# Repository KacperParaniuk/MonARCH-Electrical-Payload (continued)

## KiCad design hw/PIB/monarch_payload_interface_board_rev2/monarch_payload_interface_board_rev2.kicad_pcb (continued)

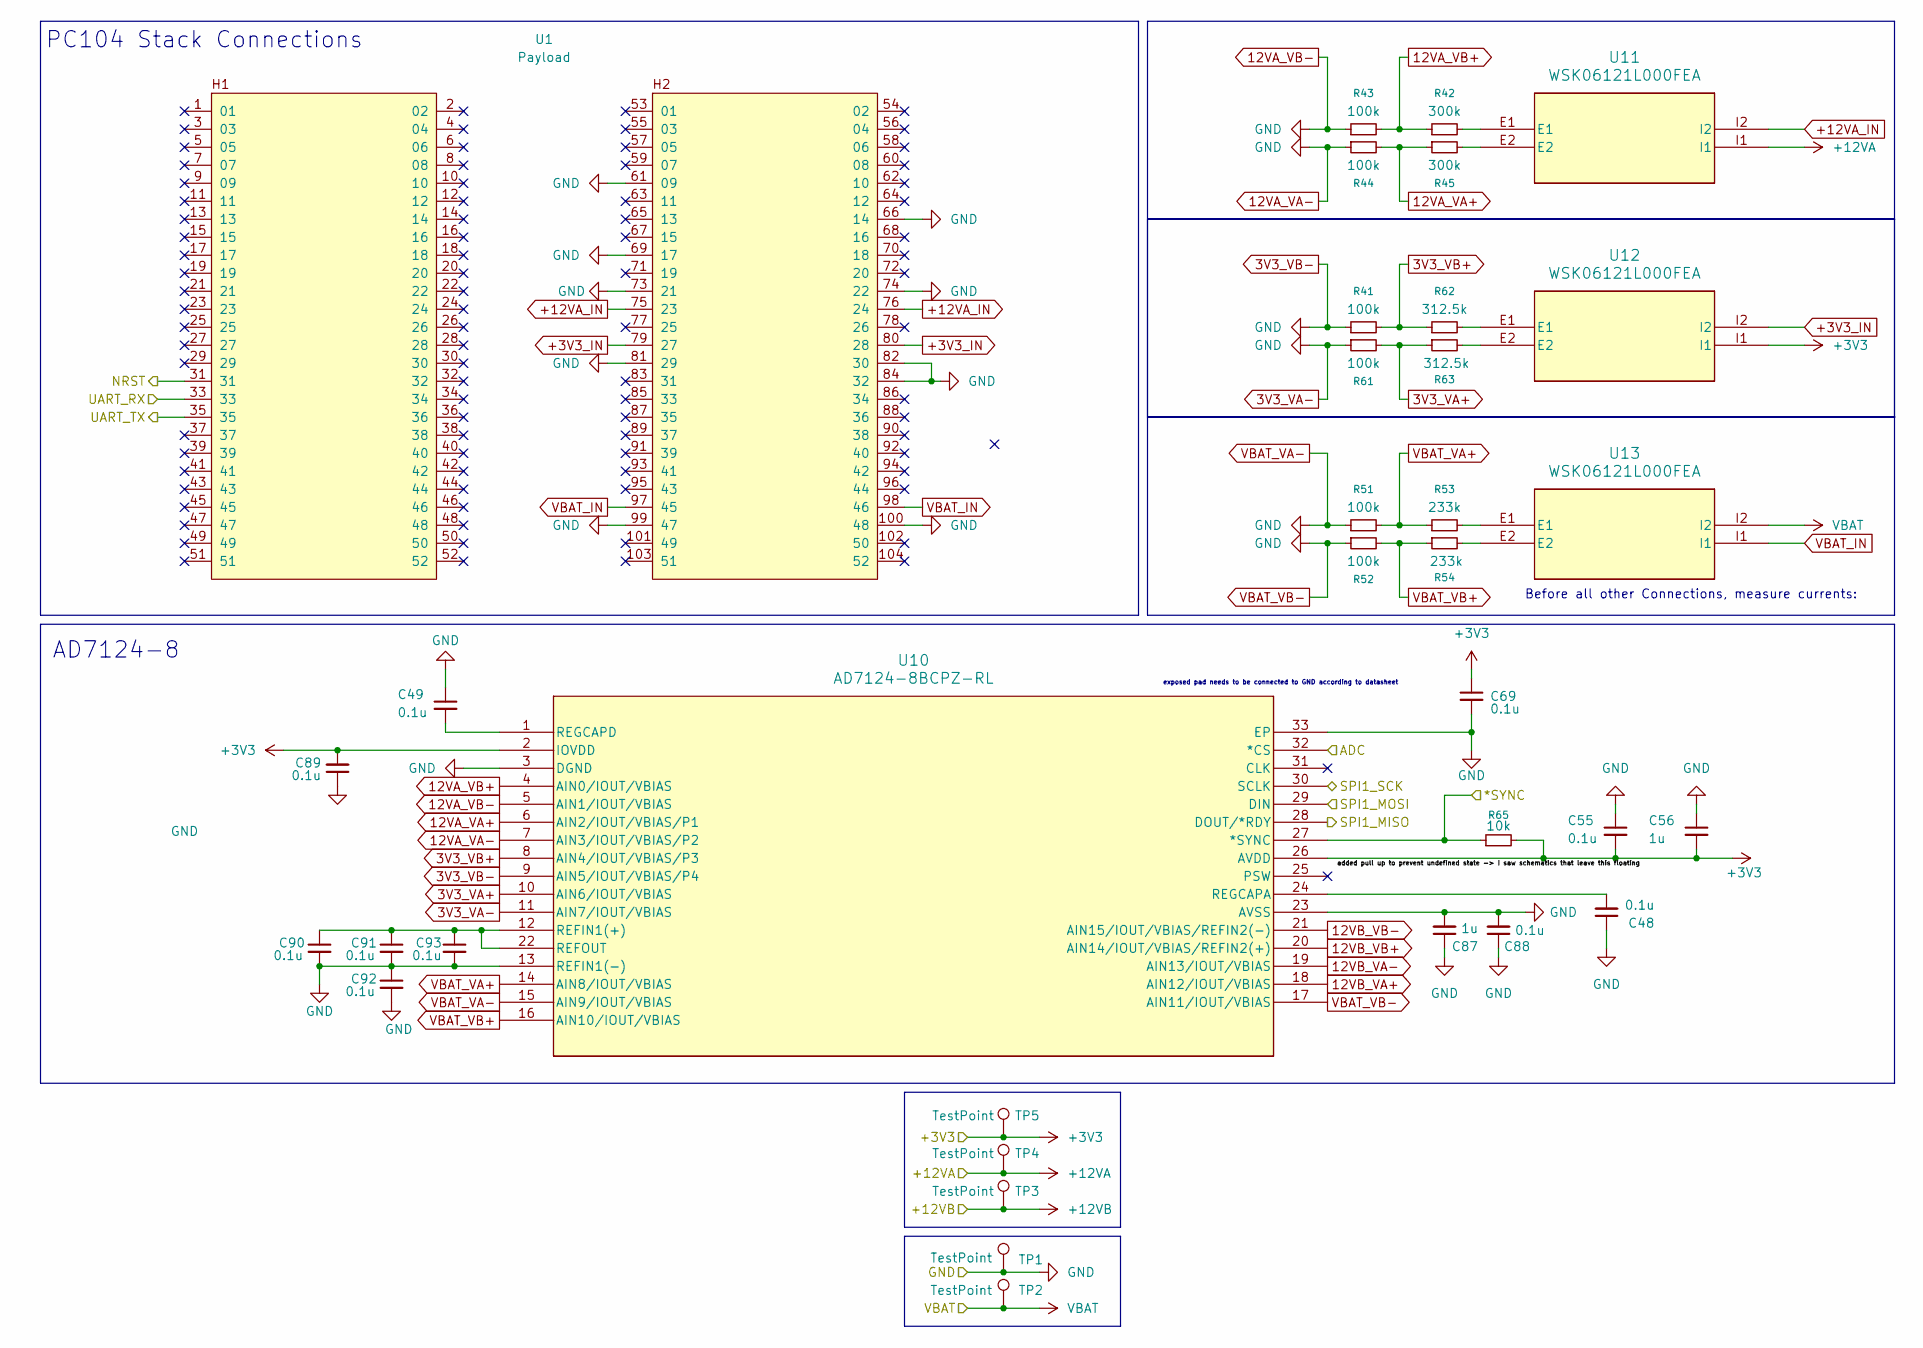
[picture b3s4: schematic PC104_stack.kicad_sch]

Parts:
C48, C49, C55, C69, C88, C89, C90, C91, C92, C93: 0.1u; C_0603_1608Metric
C56, C87: 1u; C_0603_1608Metric
R41, R43, R44, R51, R52, R61: 100k; R_0603_1608Metric
R42, R45: 300k; R_0603_1608Metric
R53, R54: 233k; R_0603_1608Metric
R62, R63: 312.5k; R_0603_1608Metric
R65: 10k; R_0603_1608Metric
TP1, TP2, TP3, TP4, TP5: TestPoint; TestPoint_Pad_D1.0mm
U1: Payload; PC104-Standard
U10: AD7124-8BCPZ-RL; CP-32-12_ADI
U11, U12, U13: WSK06121L000FEA; SMT_121L000FEA_VIS

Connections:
3V3_VA+: R61.2, R63.1, U10.10 (AIN6/IOUT/VBIAS)
3V3_VB+: R41.2, R62.1, U10.8 (AIN4/IOUT/VBIAS/P3)
12VA_VA+: R44.2, R45.1, U10.6 (AIN2/IOUT/VBIAS/P1)
12VA_VA-: C48.1, C49.1, C55.1, C56.1, C69.2, C87.1, C87.2, C88.1, C88.2, C89.1, C90.2, C91.2, C92.1, C92.2, C93.2, R41.1, R43.1, R44.1, R51.1, R52.1, R61.1, TP1.1 (1_1), U1.61 (09), U1.66 (14), U1.69 (17), U1.73 (21), U1.74 (22), U1.81 (29), U1.82 (30), U1.84 (32), U1.99 (47), U1.100 (48), U10.3 (DGND), U10.5 (AIN1/IOUT/VBIAS), U10.7 (AIN3/IOUT/VBIAS/P2), U10.9 (AIN5/IOUT/VBIAS/P4), U10.11 (AIN7/IOUT/VBIAS), U10.13 (REFIN1(-)), U10.15 (AIN9/IOUT/VBIAS), U10.17 (AIN11/IOUT/VBIAS), U10.19 (AIN13/IOUT/VBIAS), U10.21 (AIN15/IOUT/VBIAS/REFIN2(-)), U10.23 (AVSS), U10.33 (EP); also elsewhere on the board
12VA_VB+: R42.1, R43.2, U10.4 (AIN0/IOUT/VBIAS)
12VB_VA+: U10.18 (AIN12/IOUT/VBIAS); also elsewhere on the board
12VB_VB+: U10.20 (AIN14/IOUT/VBIAS/REFIN2(+)); also elsewhere on the board
+3V3: C55.2, C56.2, C69.1, C89.2, R65.2, TP5.1 (1_1), U10.2 (IOVDD), U10.26 (AVDD), U12.I1; also elsewhere on the board
+3V3_IN: U1.79 (27), U1.80 (28), U12.I2
+12VA: TP4.1 (1_1), U11.I1; also elsewhere on the board
+12VA_IN: U1.75 (23), U1.76 (24), U11.I2
+12VB: TP3.1 (1_1); also elsewhere on the board
/Connectors/*SYNC: R65.1, U10.27 (*SYNC); also elsewhere on the board
/Connectors/ADC: U10.32 (*CS); also elsewhere on the board
/Connectors/SPI1_MISO: U10.28 (DOUT/*RDY); also elsewhere on the board
/Connectors/SPI1_MOSI: U10.29 (DIN); also elsewhere on the board
/Connectors/SPI1_SCK: U10.30 (SCLK); also elsewhere on the board
/Connectors/USART3_RX: U1.35; also elsewhere on the board
/Connectors/USART3_TX: U1.33; also elsewhere on the board
/MCU/NRST: U1.31; also elsewhere on the board
unnamed: R42.2, U11.E1
unnamed: R45.2, U11.E2
unnamed: R53.2, U13.E1
unnamed: R54.2, U13.E2
unnamed: R62.2, U12.E1
unnamed: R63.2, U12.E2
unnamed: C90.1, C91.1, C93.1, U10.12 (REFIN1(+)), U10.22 (REFOUT)
unnamed: C48.2, U10.24 (REGCAPA)
unnamed: C49.2, U10.1 (REGCAPD)
VBAT: TP2.1 (1_1), U13.I2; also elsewhere on the board
VBAT_IN: U1.97 (45), U1.98 (46), U13.I1
VBAT_VA+: R51.2, R53.1, U10.14 (AIN8/IOUT/VBIAS)
VBAT_VB+: R52.2, R54.1, U10.16 (AIN10/IOUT/VBIAS)

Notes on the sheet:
Before all other Connections, measure currents:
AD7124-8
PC104 Stack Connections
exposed pad needs to be connected to GND according to datasheet

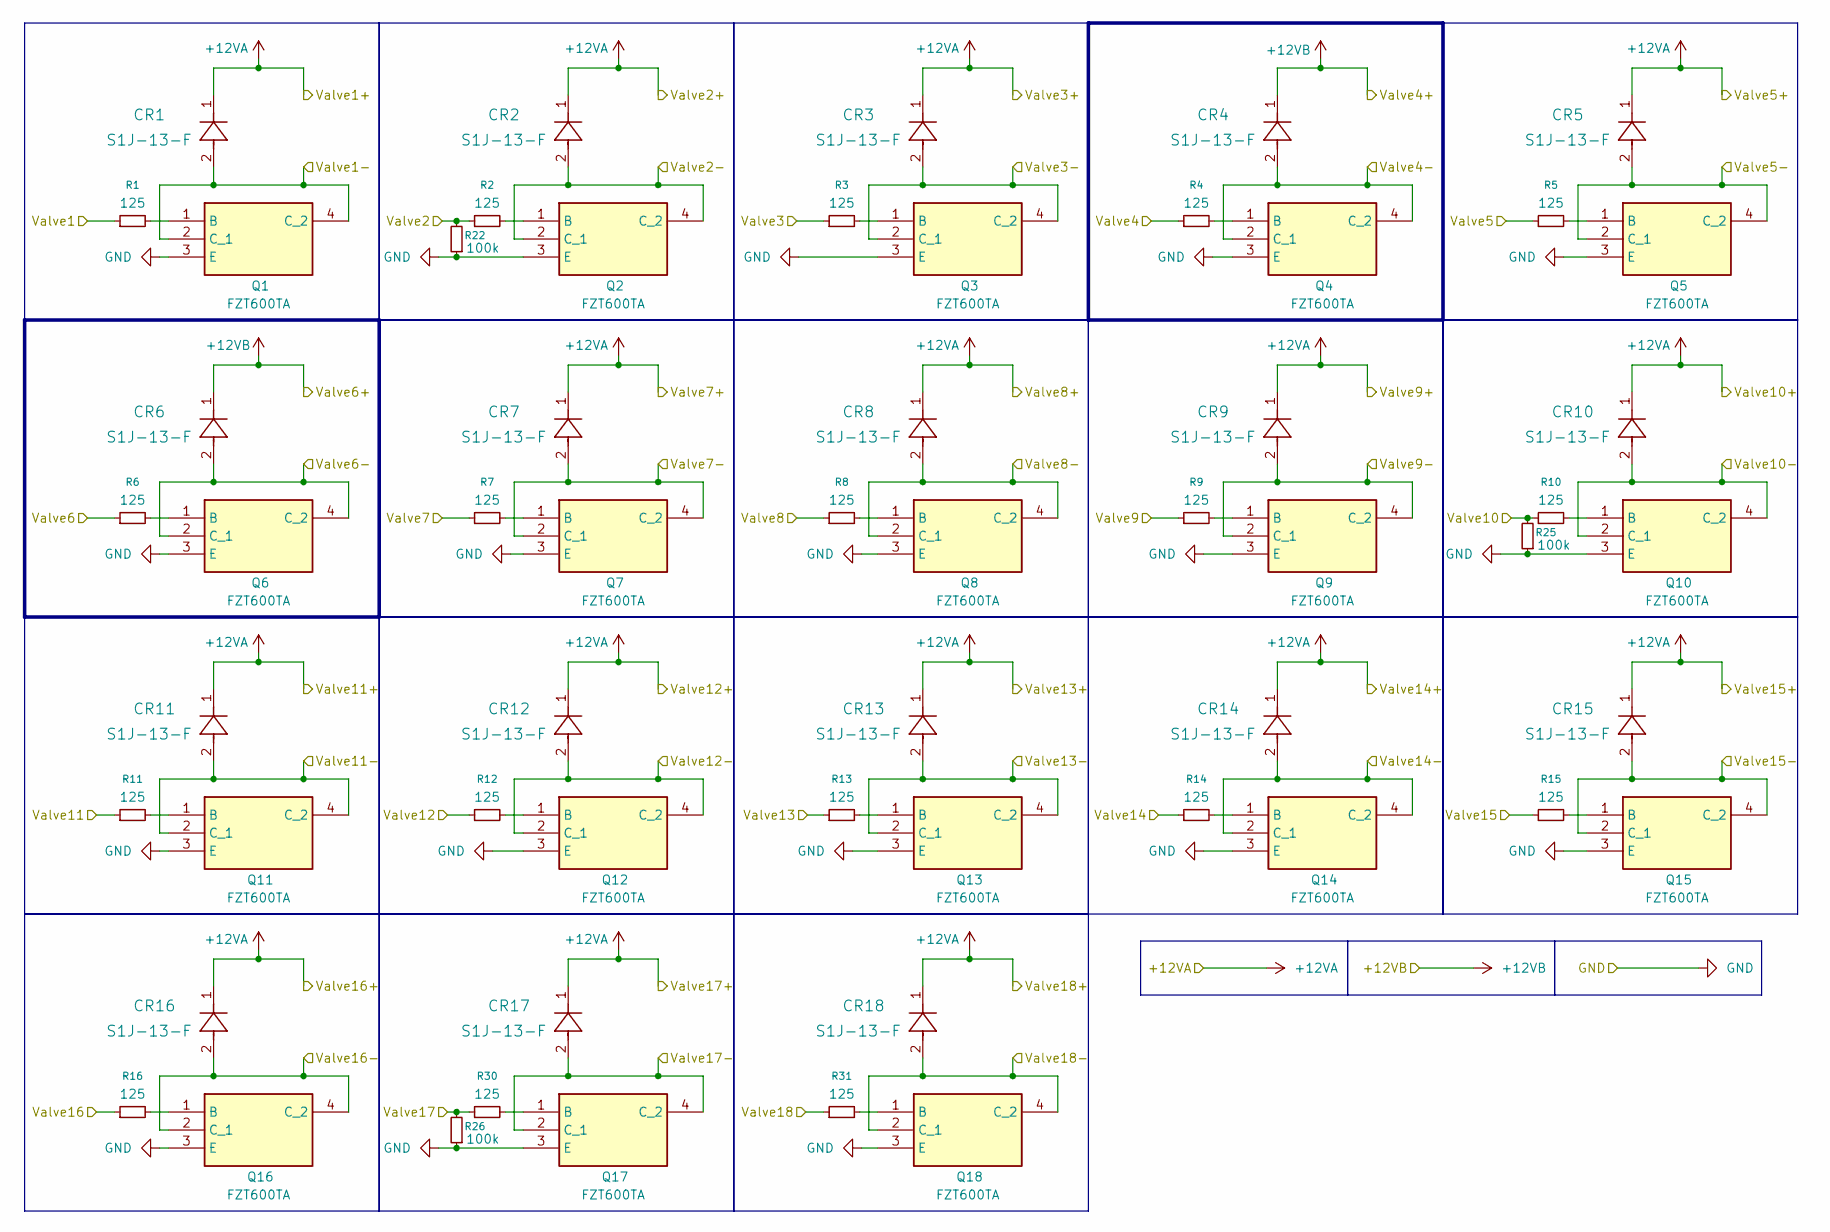
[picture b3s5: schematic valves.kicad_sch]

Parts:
CR1, CR2, CR3, CR4, CR5, CR6, CR7, CR8, CR9, CR10, CR11, CR12, CR13, CR14, CR15, CR16, CR17, CR18: S1J-13-F; SMA_DIO-L
Q1, Q2, Q3, Q4, Q5, Q6, Q7, Q8, Q9, Q10, Q11, Q12, Q13, Q14, Q15, Q16, Q17, Q18: FZT600TA; SOT230P700X170-4N; Mouser Part Number 522-FZT600TA
R1, R2, R3, R4, R5, R6, R7, R8, R9, R10, R11, R12, R13, R14, R15, R16, R30, R31: 125; R_0603_1608Metric
R22, R25, R26: 100k; R_0603_1608Metric

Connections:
12VA_VA-: Q1.3 (E), Q2.3 (E), Q3.3 (E), Q4.3 (E), Q5.3 (E), Q6.3 (E), Q7.3 (E), Q8.3 (E), Q9.3 (E), Q10.3 (E), Q11.3 (E), Q12.3 (E), Q13.3 (E), Q14.3 (E), Q15.3 (E), Q16.3 (E), Q17.3 (E), Q18.3 (E), R22.1, R25.1, R26.1; also elsewhere on the board
+12VA: CR1.1, CR2.1, CR3.1, CR5.1, CR7.1, CR8.1, CR9.1, CR10.1, CR11.1, CR12.1, CR13.1, CR14.1, CR15.1, CR16.1, CR17.1, CR18.1; also elsewhere on the board
+12VB: CR4.1, CR6.1; also elsewhere on the board
/Connectors/Valve1-: CR1.2, Q1.2 (C_1), Q1.4 (C_2); also elsewhere on the board
/Connectors/Valve2-: CR2.2, Q2.2 (C_1), Q2.4 (C_2); also elsewhere on the board
/Connectors/Valve3-: CR3.2, Q3.2 (C_1), Q3.4 (C_2); also elsewhere on the board
/Connectors/Valve4-: CR4.2, Q4.2 (C_1), Q4.4 (C_2); also elsewhere on the board
/Connectors/Valve5-: CR5.2, Q5.2 (C_1), Q5.4 (C_2); also elsewhere on the board
/Connectors/Valve6-: CR6.2, Q6.2 (C_1), Q6.4 (C_2); also elsewhere on the board
/Connectors/Valve7-: CR7.2, Q7.2 (C_1), Q7.4 (C_2); also elsewhere on the board
/Connectors/Valve8-: CR8.2, Q8.2 (C_1), Q8.4 (C_2); also elsewhere on the board
/Connectors/Valve9-: CR9.2, Q9.2 (C_1), Q9.4 (C_2); also elsewhere on the board
/Connectors/Valve10-: CR10.2, Q10.2 (C_1), Q10.4 (C_2); also elsewhere on the board
/Connectors/Valve11-: CR11.2, Q11.2 (C_1), Q11.4 (C_2); also elsewhere on the board
/Connectors/Valve12-: CR12.2, Q12.2 (C_1), Q12.4 (C_2); also elsewhere on the board
/Connectors/Valve13-: CR13.2, Q13.2 (C_1), Q13.4 (C_2); also elsewhere on the board
/Connectors/Valve14-: CR14.2, Q14.2 (C_1), Q14.4 (C_2); also elsewhere on the board
/Connectors/Valve15-: CR15.2, Q15.2 (C_1), Q15.4 (C_2); also elsewhere on the board
/Connectors/Valve16-: CR16.2, Q16.2 (C_1), Q16.4 (C_2); also elsewhere on the board
/Connectors/Valve17-: CR17.2, Q17.2 (C_1), Q17.4 (C_2); also elsewhere on the board
/Connectors/Valve18-: CR18.2, Q18.2 (C_1), Q18.4 (C_2); also elsewhere on the board
/MCU/Valve1: R1.1; also elsewhere on the board
/MCU/Valve2: R2.1, R22.2; also elsewhere on the board
/MCU/Valve3: R3.1; also elsewhere on the board
/MCU/Valve4: R4.1; also elsewhere on the board
/MCU/Valve5: R5.1; also elsewhere on the board
/MCU/Valve6: R6.1; also elsewhere on the board
/MCU/Valve7: R7.1; also elsewhere on the board
/MCU/Valve8: R8.1; also elsewhere on the board
/MCU/Valve9: R9.1; also elsewhere on the board
/MCU/Valve10: R10.1, R25.2; also elsewhere on the board
/MCU/Valve11: R11.1; also elsewhere on the board
/MCU/Valve12: R12.1; also elsewhere on the board
/MCU/Valve13: R13.1; also elsewhere on the board
/MCU/Valve14: R14.1; also elsewhere on the board
/MCU/Valve15: R15.1; also elsewhere on the board
/MCU/Valve16: R16.1; also elsewhere on the board
/MCU/Valve17: R26.2, R30.1; also elsewhere on the board
/MCU/Valve18: R31.1; also elsewhere on the board
unnamed: Q1.1 (B), R1.2
unnamed: Q2.1 (B), R2.2
unnamed: Q3.1 (B), R3.2
unnamed: Q4.1 (B), R4.2
unnamed: Q5.1 (B), R5.2
unnamed: Q6.1 (B), R6.2
unnamed: Q7.1 (B), R7.2
unnamed: Q8.1 (B), R8.2
unnamed: Q9.1 (B), R9.2
unnamed: Q10.1 (B), R10.2
unnamed: Q11.1 (B), R11.2
unnamed: Q12.1 (B), R12.2
unnamed: Q13.1 (B), R13.2
unnamed: Q14.1 (B), R14.2
unnamed: Q15.1 (B), R15.2
unnamed: Q16.1 (B), R16.2
unnamed: Q17.1 (B), R30.2
unnamed: Q18.1 (B), R31.2

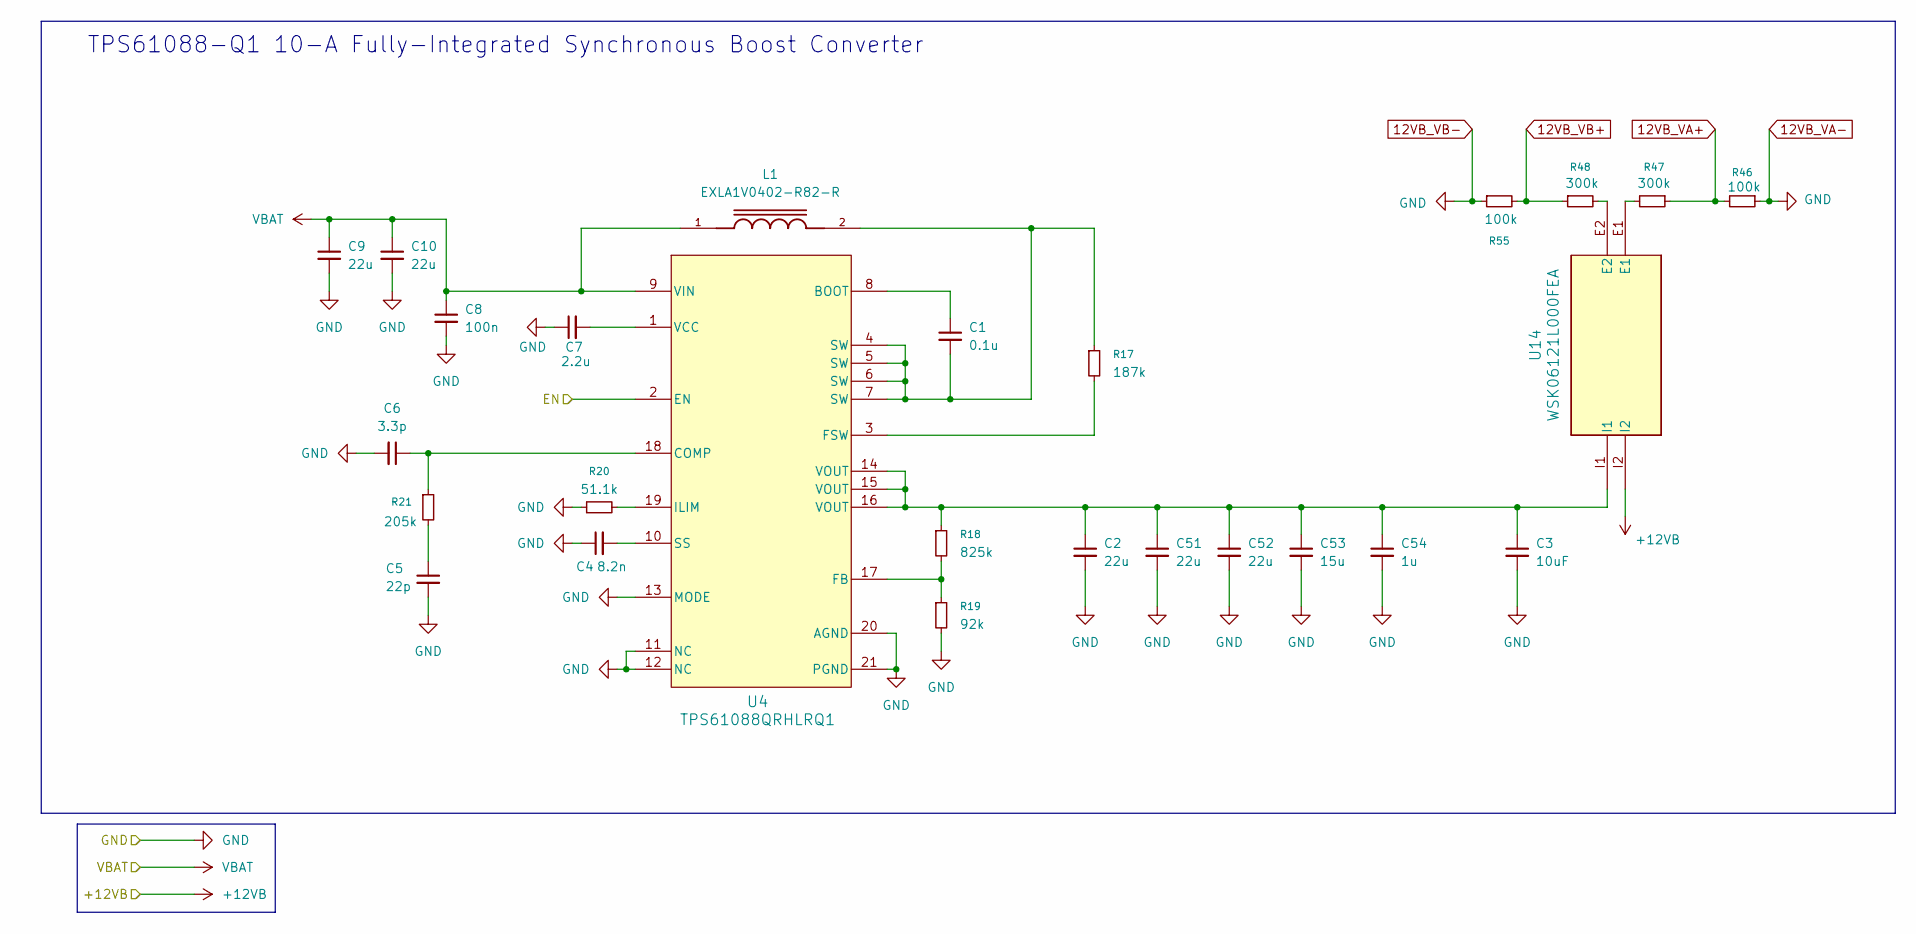
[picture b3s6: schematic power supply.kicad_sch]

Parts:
C1: 0.1u; C_0603_1608Metric
C2, C9, C10, C51, C52: 22u; C_0805_2012Metric
C3: 10uF; C_1206_3216Metric
C4: 8.2n; C_0603_1608Metric
C5: 22p; C_0603_1608Metric
C6: 3.3p; C_0603_1608Metric
C7: 2.2u; C_0603_1608Metric
C8: 100n; C_0603_1608Metric
C53: 15u; C_1206_3216Metric
C54: 1u; C_0603_1608Metric
L1: EXLA1V0402-R82-R; IND_EXLA1V0402-R82-R; PARTREV July 2022; DigiKey_Part_Number 283-EXLA1V0402-R82-RCT-ND
R17: 187k; R_0603_1608Metric
R18: 825k; R_0603_1608Metric
R19: 92k; R_0603_1608Metric
R20: 51.1k; R_0603_1608Metric
R21: 205k; R_0603_1608Metric
R46, R55: 100k; R_0603_1608Metric
R47, R48: 300k; R_0603_1608Metric
U4: TPS61088QRHLRQ1; RHL0020A
U14: WSK06121L000FEA; SMT_121L000FEA_VIS

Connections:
12VA_VA-: C2.2, C3.2, C4.1, C5.2, C6.2, C7.1, C8.2, C9.2, C10.2, C51.2, C52.2, C53.2, C54.2, R19.2, R20.1, R46.1, R55.1, U4.11 (NC), U4.12 (NC), U4.13 (MODE), U4.20 (AGND), U4.21 (PGND), U4.V; also elsewhere on the board
12VB_VA+: R46.2, R47.1; also elsewhere on the board
12VB_VB+: R48.1, R55.2; also elsewhere on the board
+12VB: U14.I2; also elsewhere on the board
/12V Power Supply/EN: U4.2 (EN); also elsewhere on the board
unnamed: C1.2, L1.2, R17.1, U4.4 (SW), U4.5 (SW), U4.6 (SW), U4.7 (SW)
unnamed: C2.1, C3.1, C51.1, C52.1, C53.1, C54.1, R18.1, U4.14 (VOUT), U4.15 (VOUT), U4.16 (VOUT), U14.I1
unnamed: C5.1, R21.2
unnamed: R47.2, U14.E1
unnamed: R48.2, U14.E2
unnamed: C1.1, U4.8 (BOOT)
unnamed: C6.1, R21.1, U4.18 (COMP)
unnamed: R18.2, R19.1, U4.17 (FB)
unnamed: R17.2, U4.3 (FSW)
unnamed: R20.2, U4.19 (ILIM)
unnamed: C4.2, U4.10 (SS)
unnamed: C7.2, U4.1 (VCC)
VBAT: C8.1, C9.1, C10.1, L1.1, U4.9 (VIN); also elsewhere on the board

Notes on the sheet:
TPS61088-Q1 10-A Fully-Integrated Synchronous Boost Converter

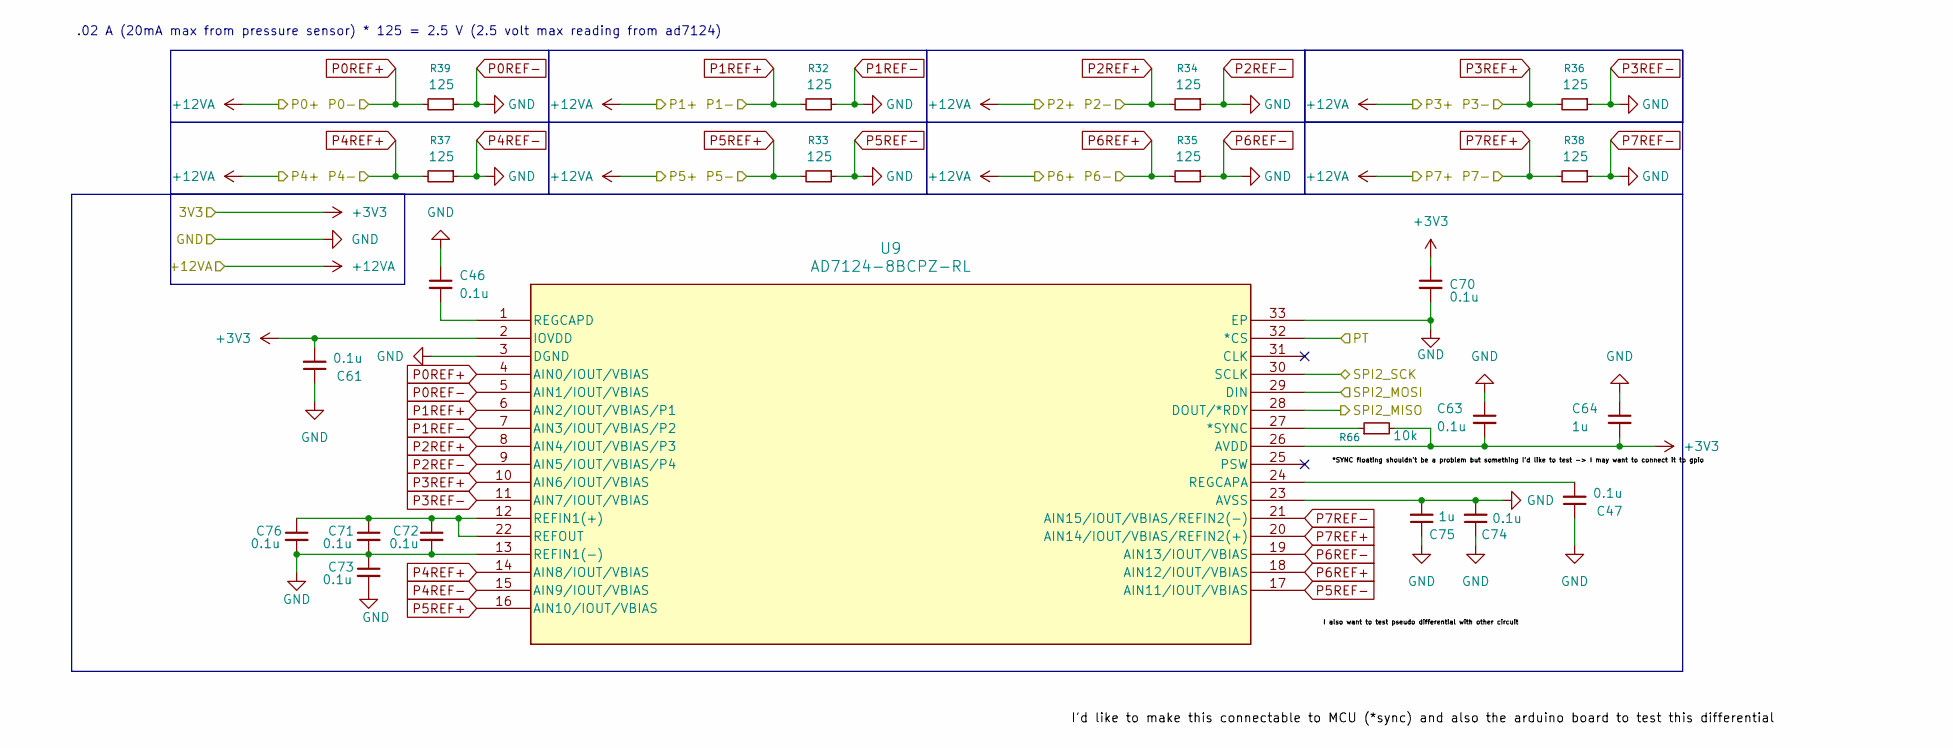
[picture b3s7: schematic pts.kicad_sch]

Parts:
C46, C47, C61, C63, C70, C71, C72, C73, C74, C76: 0.1u; C_0603_1608Metric
C64, C75: 1u; C_0603_1608Metric
R32, R33, R34, R35, R36, R37, R38, R39: 125; R_0603_1608Metric
R66: 10k; R_0603_1608Metric
U9: AD7124-8BCPZ-RL; CP-32-12_ADI

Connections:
12VA_VA-: C46.1, C47.1, C61.1, C63.1, C64.1, C70.2, C71.2, C72.2, C73.1, C73.2, C74.1, C74.2, C75.1, C75.2, C76.2, R32.1, R33.1, R34.1, R35.1, R36.1, R37.1, R38.1, R39.1, U9.3 (DGND), U9.5 (AIN1/IOUT/VBIAS), U9.7 (AIN3/IOUT/VBIAS/P2), U9.9 (AIN5/IOUT/VBIAS/P4), U9.11 (AIN7/IOUT/VBIAS), U9.13 (REFIN1(-)), U9.15 (AIN9/IOUT/VBIAS), U9.17 (AIN11/IOUT/VBIAS), U9.19 (AIN13/IOUT/VBIAS), U9.21 (AIN15/IOUT/VBIAS/REFIN2(-)), U9.23 (AVSS), U9.33 (EP); also elsewhere on the board
+3V3: C61.2, C63.2, C64.2, C70.1, R66.2, U9.2 (IOVDD), U9.26 (AVDD); also elsewhere on the board
/Connectors/PT: U9.32 (*CS); also elsewhere on the board
/Connectors/SPI2_MISO: U9.28 (DOUT/*RDY); also elsewhere on the board
/Connectors/SPI2_MOSI: U9.29 (DIN); also elsewhere on the board
/Connectors/SPI2_SCK: U9.30 (SCLK); also elsewhere on the board
unnamed: R66.1, U9.27 (*SYNC)
unnamed: C71.1, C72.1, C76.1, U9.12 (REFIN1(+)), U9.22 (REFOUT)
unnamed: C47.2, U9.24 (REGCAPA)
unnamed: C46.2, U9.1 (REGCAPD)
P0REF+: R39.2, U9.4 (AIN0/IOUT/VBIAS); also elsewhere on the board
P1REF+: R32.2, U9.6 (AIN2/IOUT/VBIAS/P1); also elsewhere on the board
P2REF+: R34.2, U9.8 (AIN4/IOUT/VBIAS/P3); also elsewhere on the board
P3REF+: R36.2, U9.10 (AIN6/IOUT/VBIAS); also elsewhere on the board
P4REF+: R37.2, U9.14 (AIN8/IOUT/VBIAS); also elsewhere on the board
P5REF+: R33.2, U9.16 (AIN10/IOUT/VBIAS); also elsewhere on the board
P6REF+: R35.2, U9.18 (AIN12/IOUT/VBIAS); also elsewhere on the board
P7REF+: R38.2, U9.20 (AIN14/IOUT/VBIAS/REFIN2(+)); also elsewhere on the board

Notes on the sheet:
.02 A (20mA max from pressure sensor) * 125 = 2.5 V (2.5 volt max reading from ad7124)

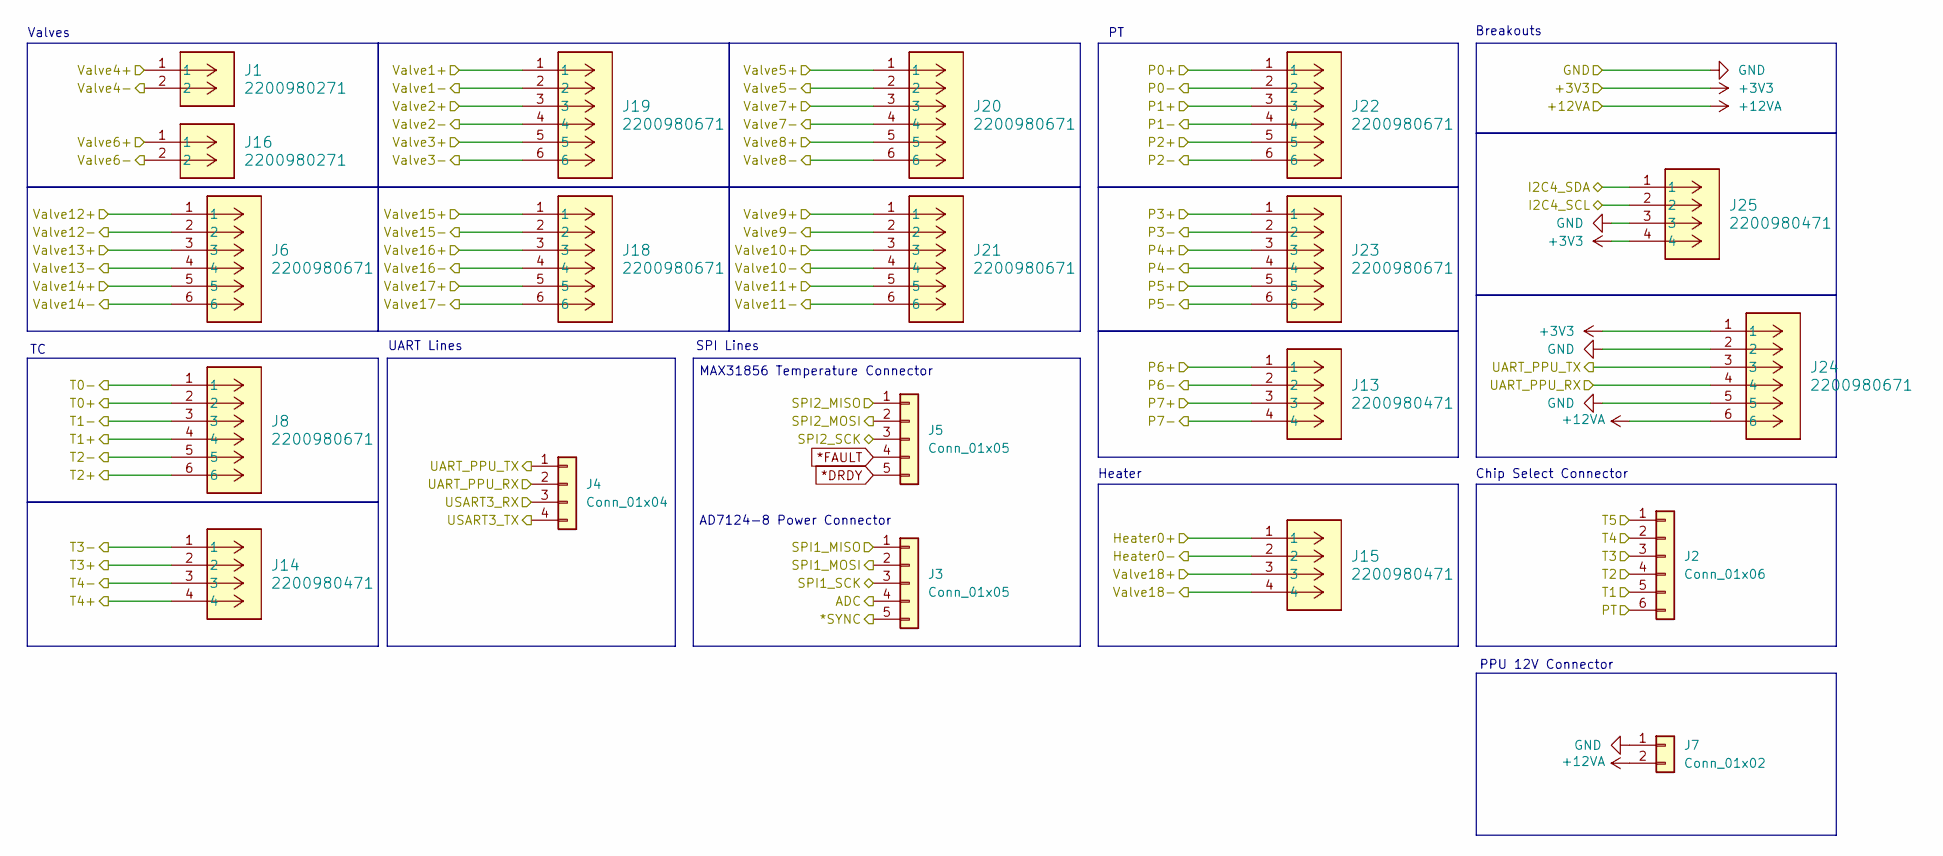
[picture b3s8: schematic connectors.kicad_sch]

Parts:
J1, J16: 2200980271; Molex_Micro-Lock_2200980271_1x02_P1.25mm_Horizontal
J2: Conn_01x06; PinHeader_1x06_P2.54mm_Vertical
J3, J5: Conn_01x05; PinHeader_1x05_P2.54mm_Vertical
J4: Conn_01x04; PinHeader_1x04_P2.54mm_Vertical
J6, J8, J18, J19, J20, J21, J22, J23, J24: 2200980671; Molex_Micro-Lock_2200980671_1x06_P1.25mm_Horizontal
J7: Conn_01x02; CONN02_534260210_MOL
J13, J14, J15, J25: 2200980471; Molex_Micro-Lock_2200980471_1x04_P1.25mm_Horizontal

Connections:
12VA_VA-: J7.1, J24.2, J24.5, J25.3; also elsewhere on the board
*DRDY: J5.5; also elsewhere on the board
*FAULT: J5.4; also elsewhere on the board
+3V3: J24.1, J25.4; also elsewhere on the board
+12VA: J6.1, J6.3, J6.5, J7.2, J13.1, J13.3, J15.1, J15.3, J18.1, J18.3, J18.5, J19.1, J19.3, J19.5, J20.1, J20.3, J20.5, J21.1, J21.3, J21.5, J22.1, J22.3, J22.5, J23.1, J23.3, J23.5, J24.6; also elsewhere on the board
+12VB: J1.1, J16.1; also elsewhere on the board
/Connectors/*SYNC: J3.5; also elsewhere on the board
/Connectors/ADC: J3.4; also elsewhere on the board
/Connectors/Heater0-: J15.2; also elsewhere on the board
/Connectors/I2C4_SCL: J25.2; also elsewhere on the board
/Connectors/I2C4_SDA: J25.1; also elsewhere on the board
/Connectors/PT: J2.6; also elsewhere on the board
/Connectors/SPI1_MISO: J3.1; also elsewhere on the board
/Connectors/SPI1_MOSI: J3.2; also elsewhere on the board
/Connectors/SPI1_SCK: J3.3; also elsewhere on the board
/Connectors/SPI2_MISO: J5.1; also elsewhere on the board
/Connectors/SPI2_MOSI: J5.2; also elsewhere on the board
/Connectors/SPI2_SCK: J5.3; also elsewhere on the board
/Connectors/T0+: J8.2; also elsewhere on the board
/Connectors/T0-: J8.1; also elsewhere on the board
/Connectors/T1: J2.5; also elsewhere on the board
/Connectors/T1+: J8.4; also elsewhere on the board
/Connectors/T1-: J8.3; also elsewhere on the board
/Connectors/T2: J2.4; also elsewhere on the board
/Connectors/T2+: J8.6; also elsewhere on the board
/Connectors/T2-: J8.5; also elsewhere on the board
/Connectors/T3: J2.3; also elsewhere on the board
/Connectors/T3+: J14.2; also elsewhere on the board
/Connectors/T3-: J14.1; also elsewhere on the board
/Connectors/T4: J2.2; also elsewhere on the board
/Connectors/T4+: J14.4; also elsewhere on the board
/Connectors/T4-: J14.3; also elsewhere on the board
/Connectors/T5: J2.1; also elsewhere on the board
/Connectors/UART_PPU_RX: J4.2, J24.4; also elsewhere on the board
/Connectors/UART_PPU_TX: J4.1, J24.3; also elsewhere on the board
/Connectors/USART3_RX: J4.3; also elsewhere on the board
/Connectors/USART3_TX: J4.4; also elsewhere on the board
/Connectors/Valve1-: J19.2; also elsewhere on the board
/Connectors/Valve2-: J19.4; also elsewhere on the board
/Connectors/Valve3-: J19.6; also elsewhere on the board
/Connectors/Valve4-: J1.2; also elsewhere on the board
/Connectors/Valve5-: J20.2; also elsewhere on the board
/Connectors/Valve6-: J16.2; also elsewhere on the board
/Connectors/Valve7-: J20.4; also elsewhere on the board
/Connectors/Valve8-: J20.6; also elsewhere on the board
/Connectors/Valve9-: J21.2; also elsewhere on the board
/Connectors/Valve10-: J21.4; also elsewhere on the board
/Connectors/Valve11-: J21.6; also elsewhere on the board
/Connectors/Valve12-: J6.2; also elsewhere on the board
/Connectors/Valve13-: J6.4; also elsewhere on the board
/Connectors/Valve14-: J6.6; also elsewhere on the board
/Connectors/Valve15-: J18.2; also elsewhere on the board
/Connectors/Valve16-: J18.4; also elsewhere on the board
/Connectors/Valve17-: J18.6; also elsewhere on the board
/Connectors/Valve18-: J15.4; also elsewhere on the board
P0REF+: J22.2; also elsewhere on the board
P1REF+: J22.4; also elsewhere on the board
P2REF+: J22.6; also elsewhere on the board
P3REF+: J23.2; also elsewhere on the board
P4REF+: J23.4; also elsewhere on the board
P5REF+: J23.6; also elsewhere on the board
P6REF+: J13.2; also elsewhere on the board
P7REF+: J13.4; also elsewhere on the board

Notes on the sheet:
UART Lines
PPU 12V Connector
AD7124-8 Power Connector
SPI Lines
Heater
Chip Select Connector
Valves
Breakouts
MAX31856 Temperature Connector

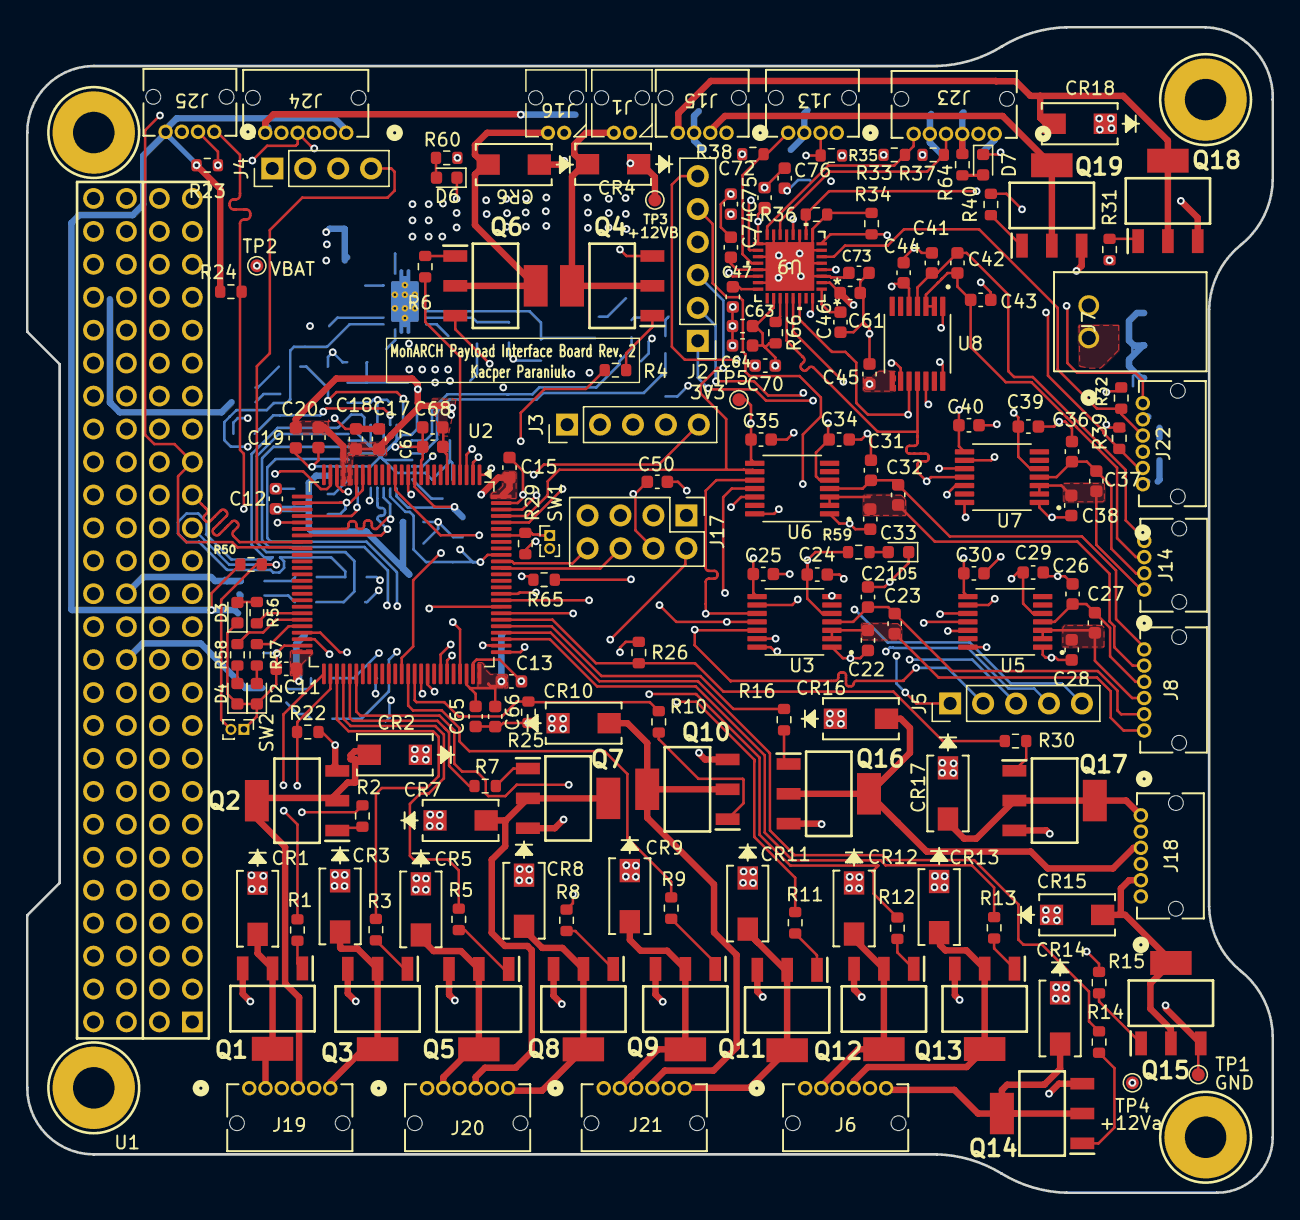
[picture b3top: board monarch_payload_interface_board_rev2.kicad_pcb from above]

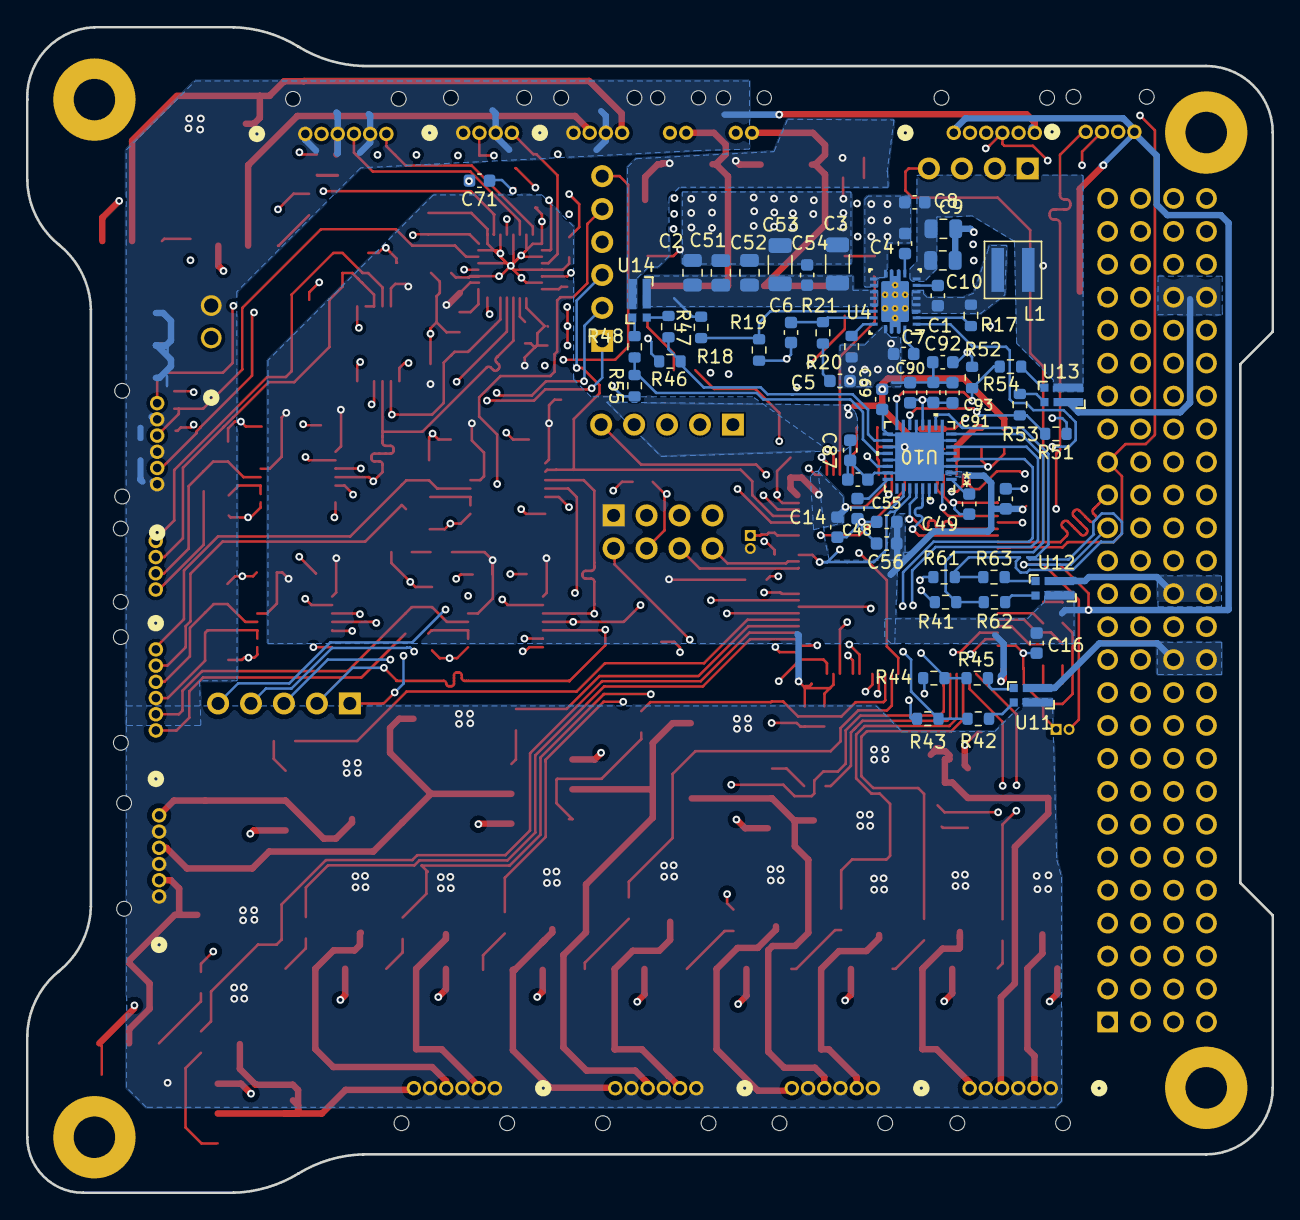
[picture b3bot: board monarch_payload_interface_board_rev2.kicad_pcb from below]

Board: 4 copper layers, 96.0 x 89.9 mm, 227 parts (57 on the bottom side), 155 nets.

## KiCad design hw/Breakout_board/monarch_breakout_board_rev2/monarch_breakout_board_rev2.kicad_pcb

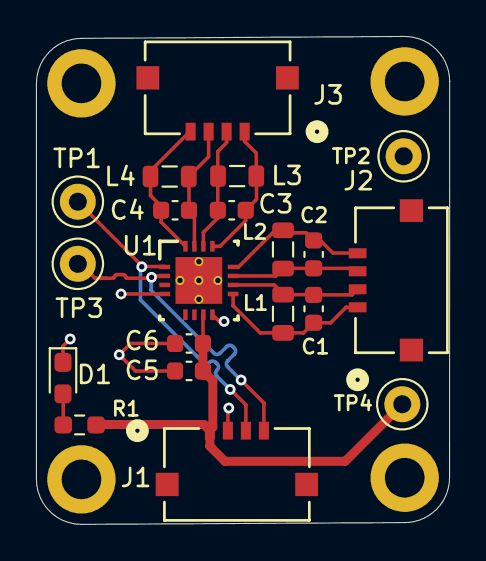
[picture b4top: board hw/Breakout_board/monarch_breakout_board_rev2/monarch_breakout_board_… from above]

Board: 2 copper layers, 23.0 x 27.1 mm, 24 parts (0 on the bottom side), 13 nets.

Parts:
C1, C2, C3, C4: 33pF; C_0603_1608Metric
C5: 1uF; C_0603_1608Metric
C6: 0.1 uF; C_0603_1608Metric
D1: RED LED; LED_0603_1608Metric_Pad1.05x0.95mm_HandSolder
H1, H2, H3, H4: MountingHole; MountingHole_2.2mm_M2_DIN965_Pad
J1, J2, J3: 5037630491; CONN_5037630000-SD_04_MOL
L1, L2, L3, L4: 18uH; L_0805_2012Metric
R1: 100; R_0603_1608Metric_Pad0.98x0.95mm_HandSolder
TP1, TP2, TP3, TP4: TestPoint; TestPoint_Keystone_5000-5004_Miniature
U1: FDC2214RGHR; RGH0016A

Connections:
+3V3: C5.2, C6.2, J1.1, R1.1, TP4.1, U1.7 (VDD)
Cap0+: C1.1, J2.1, L1.1, U1.9 (IN0A)
Cap0-: C1.2, J2.2, L1.2, U1.10 (IN0B)
Cap1+: C2.1, J2.3, L2.1, U1.11 (IN1A)
Cap1-: C2.2, J2.4, L2.2, U1.12 (IN1B)
Cap2+: C3.1, J3.1, L3.1, U1.13 (IN2A)
Cap2-: C3.2, J3.2, L3.2, U1.14 (IN2B)
Cap3+: C4.1, J3.3, L4.1, U1.15 (IN3A)
Cap3-: C4.2, J3.4, L4.2, U1.16 (IN3B)
GND: C5.1, C6.1, D1.1 (K), J1.2, TP2.1, U1.4 (ADDR), U1.8 (GND), U1.17 (PAD), U1.V
I2C4_SCL: J1.3, TP1.1, U1.1 (SCL)
I2C4_SDA: J1.4, TP3.1, U1.2 (SDA)
unnamed: D1.2 (A), R1.2
